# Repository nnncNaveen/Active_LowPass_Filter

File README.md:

# Active_LowPass_Filter

# Active Low-Pass Filter PCB (KiCad)

Op-amp based active low-pass filter built using LM358.
This project includes schematic, PCB layout, and fabrication data.

## Author
Naveen Konduru

## Tools Used
KiCad (PCB + Schematic)

## Files Included
- .kicad_pcb  – PCB layout
- .kicad_sch  – Schematic
- Gerbers (optional)
- Screenshots of PCB and 3D View

## Status
✔ Fully routed  
✔ DRC: 0 errors  
✔ Board outline correct  
✔ Ready for fabrication

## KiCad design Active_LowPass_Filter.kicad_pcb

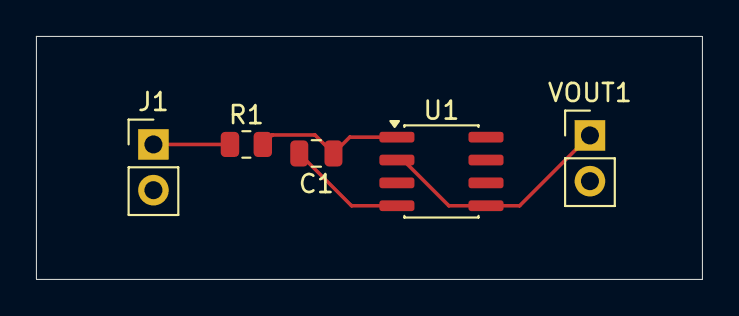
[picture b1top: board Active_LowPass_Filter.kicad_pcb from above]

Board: 2 copper layers, 37.0 x 13.5 mm, 5 parts (0 on the bottom side), 4 nets.

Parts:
C1: C; C_0805_2012Metric
J1: Conn_01x02; PinHeader_1x02_P2.54mm_Vertical
R1: R; R_0805_2012Metric
U1: SOIC-8_3.9x4.9mm_P1.27mm
VOUT1: Conn_01x02; PinHeader_1x02_P2.54mm_Vertical

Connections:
GND: C1.2, U1.4 (V-)
unnamed: J1.1, R1.1
unnamed: C1.1, R1.2, U1.1 (+)
unnamed: U1.2 (-), U1.5, VOUT1.1
